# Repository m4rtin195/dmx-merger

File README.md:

# dmx-merger

A practical part of my bachelor thesis, a device based on AVR microcontrollers, which joins two DMX512 signal streams together.

The project consists of 2 MCUs:
- `ATmega324P` that serves as a *receiver*, and "master" controller in the device, and
- `ATmega8` that serves as a *sender*, generating output DMX <u>signal</u>

More in [Bachelor thesis theory](BP_Timko_final2.pdf) (chapter 5), or in [presentation](BP_prezentacia.pdf).
<br>
<p float="left">
  
  &nbsp; &nbsp;
   
</p>

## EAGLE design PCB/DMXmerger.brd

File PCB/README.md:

**Electronic scheme:**
<br><br>

<br>

**PCB board design:**
<br><br>

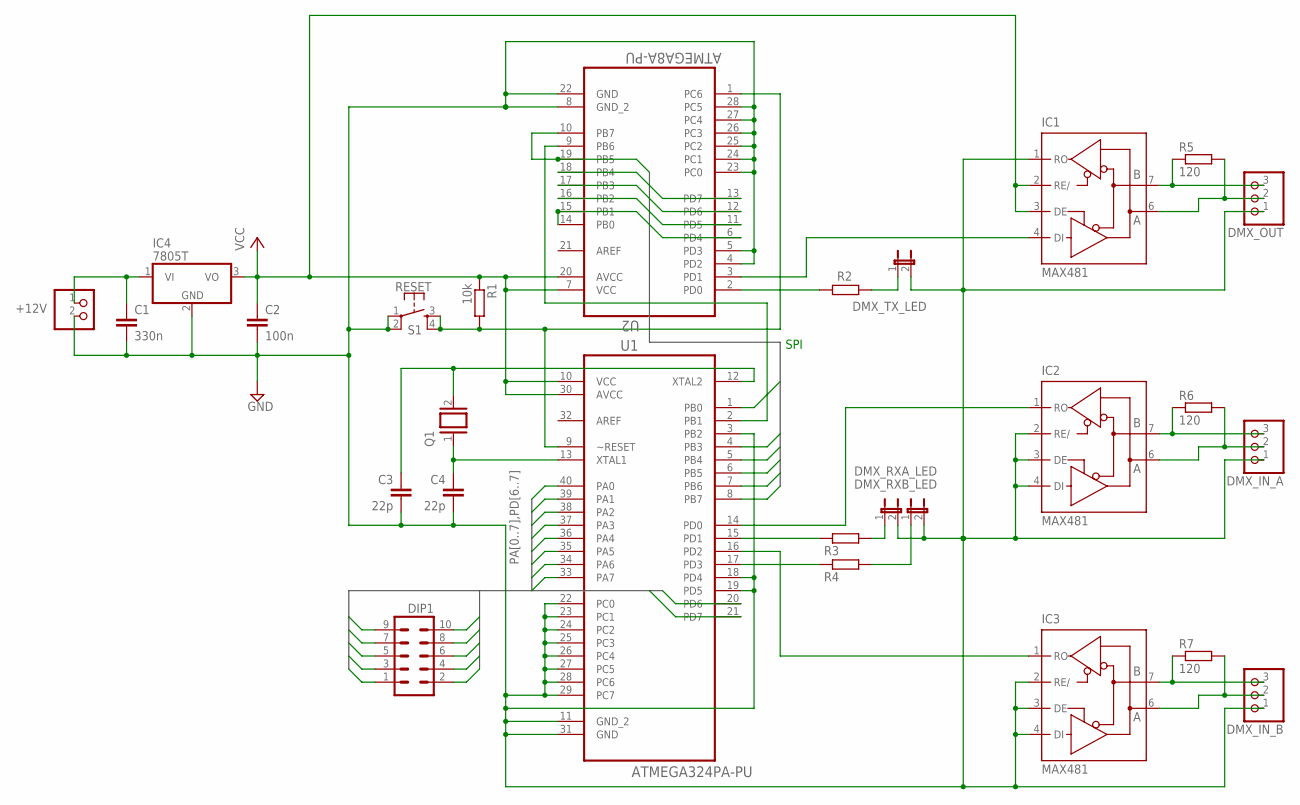
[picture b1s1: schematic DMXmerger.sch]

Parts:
+12V: PINHD-1X2; 1X02
C1: 330n; C5B3
C2: 100n; C5B3
C3, C4: 22p; C5B3
DIP1: MA05-2
DMX_IN_A: PINHD-1X3; 1X03
DMX_IN_B: PINHD-1X3; 1X03
DMX_OUT: PINHD-1X3; 1X03
DMX_RXA_LED: JP1E; JP1
DMX_RXB_LED: JP1E; JP1
DMX_TX_LED: JP1E; JP1
IC1, IC2, IC3: MAX481; DIL08
IC4: 7805T; TO220H
Q1: XTAL/S; QS
R1: 10k; 0207/12
R2, R3, R4: 250; 0207/12
R5, R6, R7: 120; 0207/12
S1: RESET; DTS-6
U1: ATMEGA324PA-PU; DIP254P1524X482-40
U2: ATMEGA8A-PU; DIP254P762X457-28

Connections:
1: DIP1.1, U1.37 (PA3)
2: DIP1.2, U1.38 (PA2)
3: DIP1.3, U1.36 (PA4)
4: DIP1.4, U1.39 (PA1)
5: DIP1.5, U1.35 (PA5)
6: DIP1.6, U1.40 (PA0)
7: DIP1.7, U1.34 (PA6)
8: DIP1.8, U1.20 (PD6)
9: DIP1.9, U1.33 (PA7)
10: DIP1.10, U1.21 (PD7)
GND: +12V.2, C1.2, C2.2, C3.2, C4.2, DMX_IN_A.1, DMX_IN_B.1, DMX_OUT.1, DMX_RXA_LED.2, DMX_RXB_LED.2, DMX_TX_LED.2, IC1.1 (RO), IC1.5 (GND), IC2.2 (RE/), IC2.3 (DE), IC2.4 (DI), IC2.5 (GND), IC3.2 (RE/), IC3.3 (DE), IC3.4 (DI), IC3.5 (GND), IC4.2 (GND), S1.1, S1.2, U1.3 (PB2), U1.11 (GND_2), U1.18 (PD4), U1.19 (PD5), U1.22 (PC0), U1.23 (PC1), U1.24 (PC2), U1.25 (PC3), U1.26 (PC4), U1.27 (PC5), U1.28 (PC6), U1.29 (PC7), U1.31 (GND), U2.4 (PD2), U2.5 (PD3), U2.8 (GND_2), U2.22 (GND), U2.23 (PC0), U2.24 (PC1), U2.25 (PC2), U2.26 (PC3), U2.27 (PC4), U2.28 (PC5)
LED: U1.1 (PB0), U2.6 (PD4)
MISO: U1.7 (PB6), U2.11 (PD5), U2.18 (PB4)
MOSI: U1.6 (PB5), U2.12 (PD6), U2.17 (PB3)
unnamed: DMX_TX_LED.1, R2.1
unnamed: DMX_IN_B.3, IC3.7 (B), R7.1
unnamed: R2.2, U2.2 (PD0)
unnamed: U1.2 (PB1), U2.9 (PB6)
unnamed: DMX_IN_B.2, IC3.6 (A), R7.2
unnamed: R1.2, S1.3, S1.4, U1.9 (~RESET), U2.1 (PC6)
unnamed: C4.1, Q1.1, U1.13 (XTAL1)
unnamed: +12V.1, C1.1, IC4.1 (VI)
unnamed: DMX_OUT.3, IC1.7 (B), R5.1
unnamed: DMX_IN_A.3, IC2.7 (B), R6.1
unnamed: DMX_IN_A.2, IC2.6 (A), R6.2
unnamed: IC1.4 (DI), U2.3 (PD1)
unnamed: DMX_OUT.2, IC1.6 (A), R5.2
unnamed: IC2.1 (RO), U1.14 (PD0)
unnamed: IC3.1 (RO), U1.16 (PD2)
unnamed: R3.2, U1.15 (PD1)
unnamed: R4.2, U1.17 (PD3)
unnamed: DMX_RXA_LED.1, R3.1
unnamed: C3.1, Q1.2, U1.12 (XTAL2)
unnamed: DMX_RXB_LED.1, R4.1
RST: U1.4 (PB3), U2.14 (PB0), U2.15 (PB1)
SCK: U1.8 (PB7), U2.10 (PB7), U2.19 (PB5)
SS: U1.5 (PB4), U2.13 (PD7), U2.16 (PB2)
VCC: C2.1, IC1.2 (RE/), IC1.3 (DE), IC1.8 (VCC), IC2.8 (VCC), IC3.8 (VCC), IC4.3 (VO), R1.1, U1.10 (VCC), U1.30 (AVCC), U2.7 (VCC), U2.20 (AVCC)

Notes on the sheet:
SPI

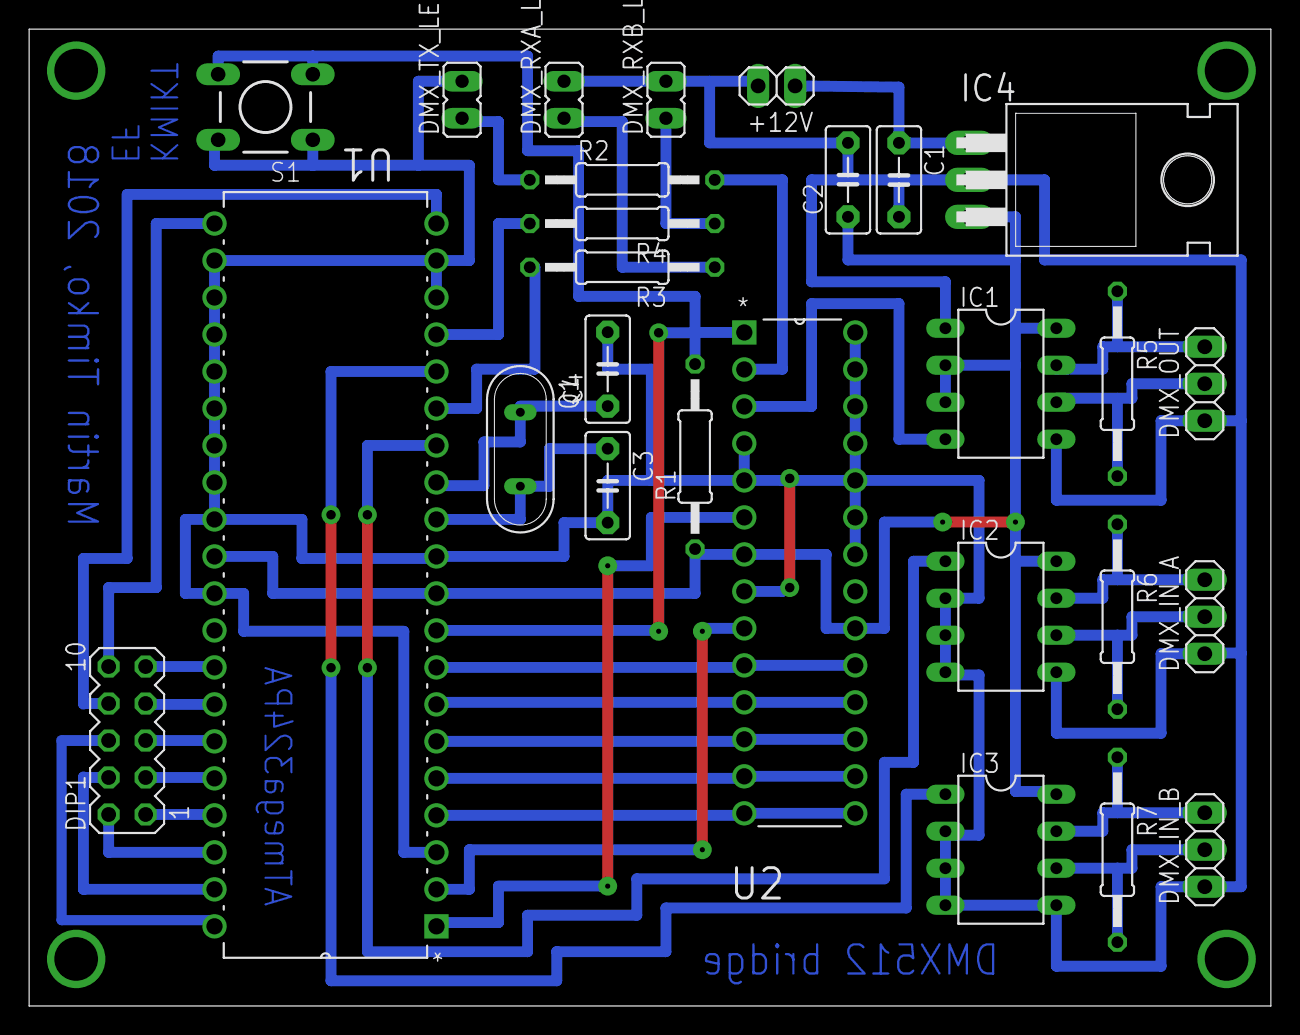
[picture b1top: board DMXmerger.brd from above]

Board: 2 copper layers, 85.3 x 67.1 mm, 27 parts (0 on the bottom side), 38 nets.

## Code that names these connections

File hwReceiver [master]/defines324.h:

//#ifndef defines32_h
//#define defines32_h

/// DMX controller defines (USART)
//#define UCSRnA UCSR0A  // USART Control and Status Register A
//    #define TXCn   TXC0    // Transmit buffer clear
//    #define UDREn  UDRE0   // USART Data Ready
//    #define FEn    FE0     // Frame Error
//
//#define UCSRnB UCSR0B  // USART Control and Status Register B
//    #define RXCIEn RXCIE0  // Enable Receive Complete Interrupt
//    #define TXCIEn TXCIE0  // Enable Transmission Complete Interrupt
//    #define UDRIEn UDRIE0  // Enable Data Register Empty Interrupt
//    #define RXENn  RXEN0   // Enable Receiving
//    #define TXENn  TXEN0   // Enable Sending
//
//#define UCSRnC UCSR0C  // USART Control and Status Register C
//    #define USBSn  USBS0   // Stop bit select 0=1bit, 1=2bits
//    #define UCSZn0 UCSZ00  // Character size 00=5, 01=6, 10=7, 11=8 bits
//    #define UPMn0  UPM00   // Parity setting 00=N, 10=E, 11=O
//
//#define UBRRn  UBRR   // USART Baud Rate Register
//    #define UBRRnH UBRR0H  // USART Baud Rate Register High
//    #define UBRRnL UBRR0L  // USART Baud Rate Register Low
//
//#define UDRn   UDR0    // USART Data Register

#define USARTn_TX_vect   USART_TXC_vect  // Interrupt Data sent

// formats for serial transmission
//#define SERIAL_8N1  ((1<<URSEL) | (0<<USBSn) | (0<<UPMn0) | (3<<UCSZn0)) //unused
#define SERIAL_8N2  ((1<<USBS0) | (0<<UPM00) | (3<<UCSZ00))
#define SERIAL_8E1  ((0<<USBS0) | (2<<UPM00) | (3<<UCSZ00))
//#define SERIAL_8E2  ((1<<URSEL) | (1<<USBSn) | (2<<UPMn0) | (3<<UCSZn0)) //unused


// the break timing is 10 bits (start + 8 data + parity) of this speed
// the mark-after-break is 1 bit of this speed plus approx 6 usec
// 100000 bit/sec is good: gives 100 usec break and 16 usec MAB
// 1990 spec says transmitter must send >= 92 usec break and >= 12 usec MAB
// receiver must accept 88 us break and 8 us MAB
#define BREAKSPEED     100000
#define DMXSPEED       250000
#define BREAKFORMAT    SERIAL_8E1   // 1 stop bit and 8 bit character size, even parity
#define DMXFORMAT      SERIAL_8N2   // 2 stop bits and 8 bit character size, no parity


#define DMXSERIAL_MAX 512

typedef enum {IDLE, BREAK, DATA} DMXReceivingState;


/// ////////////////////////////////////////////////// ///
/// SPI PART ///

//ATmega324 as master
#define SPI_DDR     DDRB
#define SPI_PORT    PORTB
#define DD_MOSI     PB5
#define DD_MISO     PB6
#define DD_SCK      PB7
#define DD_SS       PB4
//aux_delay_us(40);
#define DD_LEDPIN      PB0
#define DD_RSTPIN      PB3

/// ////////////////////////////////////////////////// ///

#define SHIFT_PIN   PA7     // DIP9
#define KEEP_PIN    PD7     // DIP10

#define RXA_LED     PD1
#define RXB_LED     PD3
//#endif

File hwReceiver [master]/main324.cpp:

#include <avr/io.h>
#include <util/delay.h>
#include <avr/interrupt.h>
#include <limits.h>

#include "defines324.h"


/// MILLIS TIMER ///

volatile unsigned long ms = 0;

unsigned long int millis(void)
{
    return ms;
}

void millis_init(void)
{
    //Timer0_Initialization
    GTCCR = (1 << PSRSYNC); // reset prescaler
    TCCR0B |= (1 << CS01);  // prescalar = 8
    TIMSK0 |= (1 << TOIE0); // timer 0 interrupt enable
}

volatile uint8_t times = 0;

ISR(TIMER0_OVF_vect)    // 0,5ms
{
    times++;
    if(times==10)
        {
            ms++;
            times=0;
        }
    TCNT0 = 155;  //250 tickov
}
/// TIMER END ///


/// /////////////// DMX CONTROLLER ///////////////// ///

#define Calcprescale(B)     ( ( (((F_CPU)/8)/(B)) - 1 ) / 2 )


volatile uint8_t    dmxData[DMXSERIAL_MAX+1];    // Array of DMX values (raw) // Entry 0 will not be used, only exist for logical simplicity reason...
uint16_t            BORDER_ADDR;           // hranièná adresa medzi príjmaèmi

volatile uint8_t    _dmxRecvState1; // Current State of receiving DMX Bytes
volatile uint8_t    _dmxRecvState2;
volatile int        _dmxChannel1;   // the next channel byte to be sent.
volatile int        _dmxChannel2;
volatile unsigned long _gotLastPacket1 = 0; // the last time (using the millis function) a packet was received.
volatile unsigned long _gotLastPacket2 = 0;


void DMX_Receivers_init()
{
  // initialize global variables
  _dmxRecvState1, _dmxRecvState2 = IDLE; // initial state
  _dmxChannel1, _dmxChannel2 = 0;

  // initialize the DMX buffer
  for (int n = 0; n < DMXSERIAL_MAX+1; n++)
    dmxData[n] = 0;

  // Set baud-settings and data format
  uint16_t baud_setting = Calcprescale(DMXSPEED);

  UCSR0A = 0;
  UBRR0L = baud_setting;
  UBRR0H = baud_setting >> 8;
  UCSR0C = DMXFORMAT;

  UCSR1A = 0;
  UBRR1L = baud_setting;
  UBRR1H = baud_setting >> 8;
  UCSR1C = DMXFORMAT;

  // Enable receivers and Receive interrupts
  UCSR0B = (1<<RXEN0) | (1<<RXCIE0);
  UCSR1B = (1<<RXEN1) | (1<<RXCIE1);
} // init()


// Calculate how long no data packet was received
unsigned long noDataSince1()
{
    if(_gotLastPacket1 == 0) return LONG_MAX;
    unsigned long now = millis();
    return (now - _gotLastPacket1);
} // noDataSince()

// Calculate how long no data packet was received
unsigned long noDataSince2()
{
    if(_gotLastPacket2 == 0) return LONG_MAX;
    unsigned long now = millis();
    return (now - _gotLastPacket2);
} // noDataSince()


/******/

// This Interrupt Service Routine is called when a byte or frame error was received.
ISR(USART0_RX_vect)
{
  uint8_t  USARTstate = UCSR0A;         //get state before data!
  uint8_t  DmxByte    = UDR0;	        //get data
  uint8_t  DmxState   = _dmxRecvState1;	//just load once from SRAM to increase speed

  if (USARTstate & (1<<FE0)) //check for break
  {
      _dmxRecvState1 = BREAK; // break condition detected.
      _dmxChannel1 = 0;       // The next data byte is the start byte

  }
  else if (DmxState == BREAK)
  {
      if (DmxByte == 0)
      {
          _dmxRecvState1 = DATA;  // normal DMX start code detected
          _dmxChannel1 = 1;       // start with channel # 1
          _gotLastPacket1 = millis(); // remember current (relative) time in msecs.
      }
      else
      {
        _dmxRecvState1 = IDLE; // This might be a RDM command
      } // if
  }
  else if (DmxState == DATA)
  {
      if(_dmxChannel1 >= 1 && _dmxChannel1 < (signed)BORDER_ADDR)
        dmxData[_dmxChannel1] = DmxByte;	// store received data into dmx data buffer.

      _dmxChannel1++;
      if(_dmxChannel1>DMXSERIAL_MAX) DmxState = IDLE; //error
   } // if
} // ISR(USARTn_RX_vect)

/**/

ISR(USART1_RX_vect)
{
  uint8_t  USARTstate = UCSR1A;         //get state before data!
  uint8_t  DmxByte    = UDR1;	        //get data
  uint8_t  DmxState   = _dmxRecvState2;	//just load once from SRAM to increase speed

  if (USARTstate & (1<<FE1)) //check for break
  {
      _dmxRecvState2 = BREAK; // break condition detected.
      _dmxChannel2 = 0;       // The next data byte is the start byte
  }
  else if (DmxState == BREAK)
  {
      if (DmxByte == 0)
      {
          _dmxRecvState2 = DATA;  // normal DMX start code detected
          _dmxChannel2 = 1;       // start with channel # 1
          _gotLastPacket2 = millis(); // remember current (relative) time in msecs.
      }
      else
      {
        _dmxRecvState2 = IDLE; // This might be a RDM command
      } // if
  }
  else if (DmxState == DATA)
  {
      if(!!(PINA & (1 << SHIFT_PIN)))   //shift off
      {
        if(_dmxChannel2 >= (signed)BORDER_ADDR && _dmxChannel2 <= DMXSERIAL_MAX)
            dmxData[_dmxChannel2] = DmxByte;	// store received data into dmx data buffer.
      }
      else                              //shift on
      {
        if(_dmxChannel2 >= 1 && _dmxChannel2 < (signed)BORDER_ADDR)
            dmxData[_dmxChannel2+BORDER_ADDR] = DmxByte;
      }

      _dmxChannel2++;
      if(_dmxChannel2>DMXSERIAL_MAX) DmxState = IDLE; //error
   } // if
} // ISR(USARTn_RX_vect)


/// END OF DMX PART /// /////////////////////////////////////////////////////////////





/// BEGINNING OF SPI PART ///

volatile unsigned int SPIchannel;
volatile bool inprogress;


void initSPI(void)
{
    SPI_PORT |= (1<<DD_SS);     //set SS high, inak nepovoli nastavenie MSTR
    SPI_DDR |= (1<<DD_MOSI) | (1<<DD_SCK) | (1<<DD_SS) | (1 << DD_RSTPIN) ; // SCK, MOSI and SS and RST as outputs
    SPI_DDR &= ~(1<<DD_MISO);   // MISO as input
    SPI_PORT |= (1 << DD_MISO); // enable pull-up on MISO

    //SPCR0 |= (1 << SPIE0);    // SPI interrupt enable
    SPCR0 |= (1 << SPE0);       // SPI enable
    SPCR0 |= (1 << MSTR0);      // Set as master
    SPCR0 &= ~(1<< DORD0);      // Data Order MSB first
    //SPSR0 |= (1 << SPI2X0);   // double speed enable

    SPCR0 |= (1<<SPR00);        // divide clock by 64

    inprogress = false;
}

void writeByteSPI()
{
    if(SPIchannel == 0)
    {
        SPI_PORT |= (1 << DD_RSTPIN);
        SPI_PORT &= ~(1 << DD_SS);
        SPDR0 = 0;
        while(!(SPSR0 & (1<<SPIF0)));
        SPI_PORT |=  (1 << DD_SS) | (1 << DD_RSTPIN);
        SPIchannel++;
    }
    else
    {
        SPI_PORT &= ~((1 << DD_SS) | (1 << DD_RSTPIN));
        SPDR0 = dmxData[SPIchannel++];	// Nahraj bajt do SPI dátového registra
        while(!(SPSR0 & (1<<SPIF0))); 	// Cakaj na ukoncenie prenosu
        SPI_PORT |=  (1 << DD_SS);
    }
    if(SPIchannel > DMXSERIAL_MAX) SPIchannel = 0;
}

void writeByteSPI(unsigned char byte)
{
    SPI_PORT &= ~(1 << DD_SS);
    SPDR0 = byte;					// Nahraj bajt do SPI dátového registra
    while(!(SPSR0 & (1<<SPIF0))); 	// Cakaj na ukoncenie prenosu
    SPI_PORT |=  (1 << DD_SS);
}


/// END OF PERIPHERIALS ////


uint16_t getAddr(void)
{
    uint16_t addr;
    addr = ( ((!(PINA & (1 << PA3))) << 0) | ((!(PINA & (1 << PA2))) << 1) | ((!(PINA & (1 << PA4))) << 2) | ((!(PINA & (1 << PA1))) << 3) | \
             ((!(PINA & (1 << PA5))) << 4) | ((!(PINA & (1 << PA0))) << 5) | ((!(PINA & (1 << PA6))) << 6) | ((!(PIND & (1 << PD6))) << 7) ) ;
    return addr;
}


int main(void)
{
    //OSCCAL = 0x49;  ///odmerat - OK na intRC

    DDRB |= (1 << DD_LEDPIN);   //set as output (signalizacia tx led)
    DDRD |= (1 << RXA_LED);     //set as output (leds)
    DDRD |= (1 << RXB_LED);

    //DIP input setting
    DDRA = 0x00;            //as input //dip
    PORTA = 0xFF;           //pullup //dip
    DDRD &= ~((1<<PD6) | (1<<KEEP_PIN)); //dip 8,10
    PORTD |= (1<<PD6) | (1<<KEEP_PIN);   //pullups
    //

    //inits
    millis_init();
    initSPI();
	DMX_Receivers_init();
	sei();


	while(1)
    {
        _delay_us(30);
        BORDER_ADDR = getAddr();
        writeByteSPI();

        if(!!(PIND & (1 << KEEP_PIN)))
        {
            if(noDataSince1()>1000)
            {
                for(int i=1; i<BORDER_ADDR; i++)
                    dmxData[i] = 0;
            }
            if(noDataSince2()>1000)
            {
                for(int i=BORDER_ADDR; i<DMXSERIAL_MAX; i++)
                    dmxData[i] = 0;
            }
        }

        //refresh led state
        if(noDataSince1()<1000) PORTD |= (1 << RXA_LED);
        else PORTD &= ~(1<<RXA_LED);
        if(noDataSince2()<1000) PORTD |= (1 << RXB_LED);
        else PORTD &= ~(1<<RXB_LED);

        //signal pre tx led
        if(noDataSince1()<1000 || noDataSince2()<1000)
            PORTB |= (1 << DD_LEDPIN);
        else
            PORTB &= ~(1 << DD_LEDPIN);
	}

	return 0;
}

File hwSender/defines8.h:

//#ifndef defines8_h
//#define defines8_h

/// DMX controller defines (USART) /////////////////////


#define USARTn_TX_vect   USART_TXC_vect  // Interrupt Data sent
#define USARTn_UDRE_vect USART_UDRE_vect // Interrupt Data Register empty


// formats for serial transmission
#define SERIAL_8N2  ((1<<URSEL) | (1<<USBS) | (0<<UPM0) | (3<<UCSZ0)) // 1 stop bit and 8 bit character size, even parity
#define SERIAL_8E1  ((1<<URSEL) | (0<<USBS) | (2<<UPM0) | (3<<UCSZ0)) // 2 stop bits and 8 bit character size, no parity


// the break timing is 10 bits (start + 8 data + parity) of this speed
// the mark-after-break is 1 bit of this speed plus approx 6 usec
// 100000 bit/sec is good: gives 100 usec break and 16 usec MAB
// 1990 spec says transmitter must send >= 92 usec break and >= 12 usec MAB
// receiver must accept 88 us break and 8 us MAB
#define BREAKSPEED     100000
#define DMXSPEED       250000
#define BREAKFORMAT    SERIAL_8E1
#define DMXFORMAT      SERIAL_8N2


#define DMXSERIAL_MAX 512


/// ////////////////////////////////////////////////// ///
/// SPI PART ///

//ATmega8 as slave
#define SPI_DDR    DDRB
#define SPI_PORT   PORTB
#define SPI_PIN    PINB
#define DD_MOSI    PB3
#define DD_MISO    PB4
#define DD_SCK     PB5
#define DD_SS      PB2

#define DD_RSTPIN  PB1
#define DD_LEDPIN  PD4

/// ////////////////////////////////////////////////// ///

#define TX_LED     PD0

//#endif

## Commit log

2021-12-06 upload
2021-12-06 readme pcb
